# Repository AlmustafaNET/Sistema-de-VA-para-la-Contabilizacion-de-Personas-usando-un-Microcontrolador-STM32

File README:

# Este es mi README

<b> hola  </b>

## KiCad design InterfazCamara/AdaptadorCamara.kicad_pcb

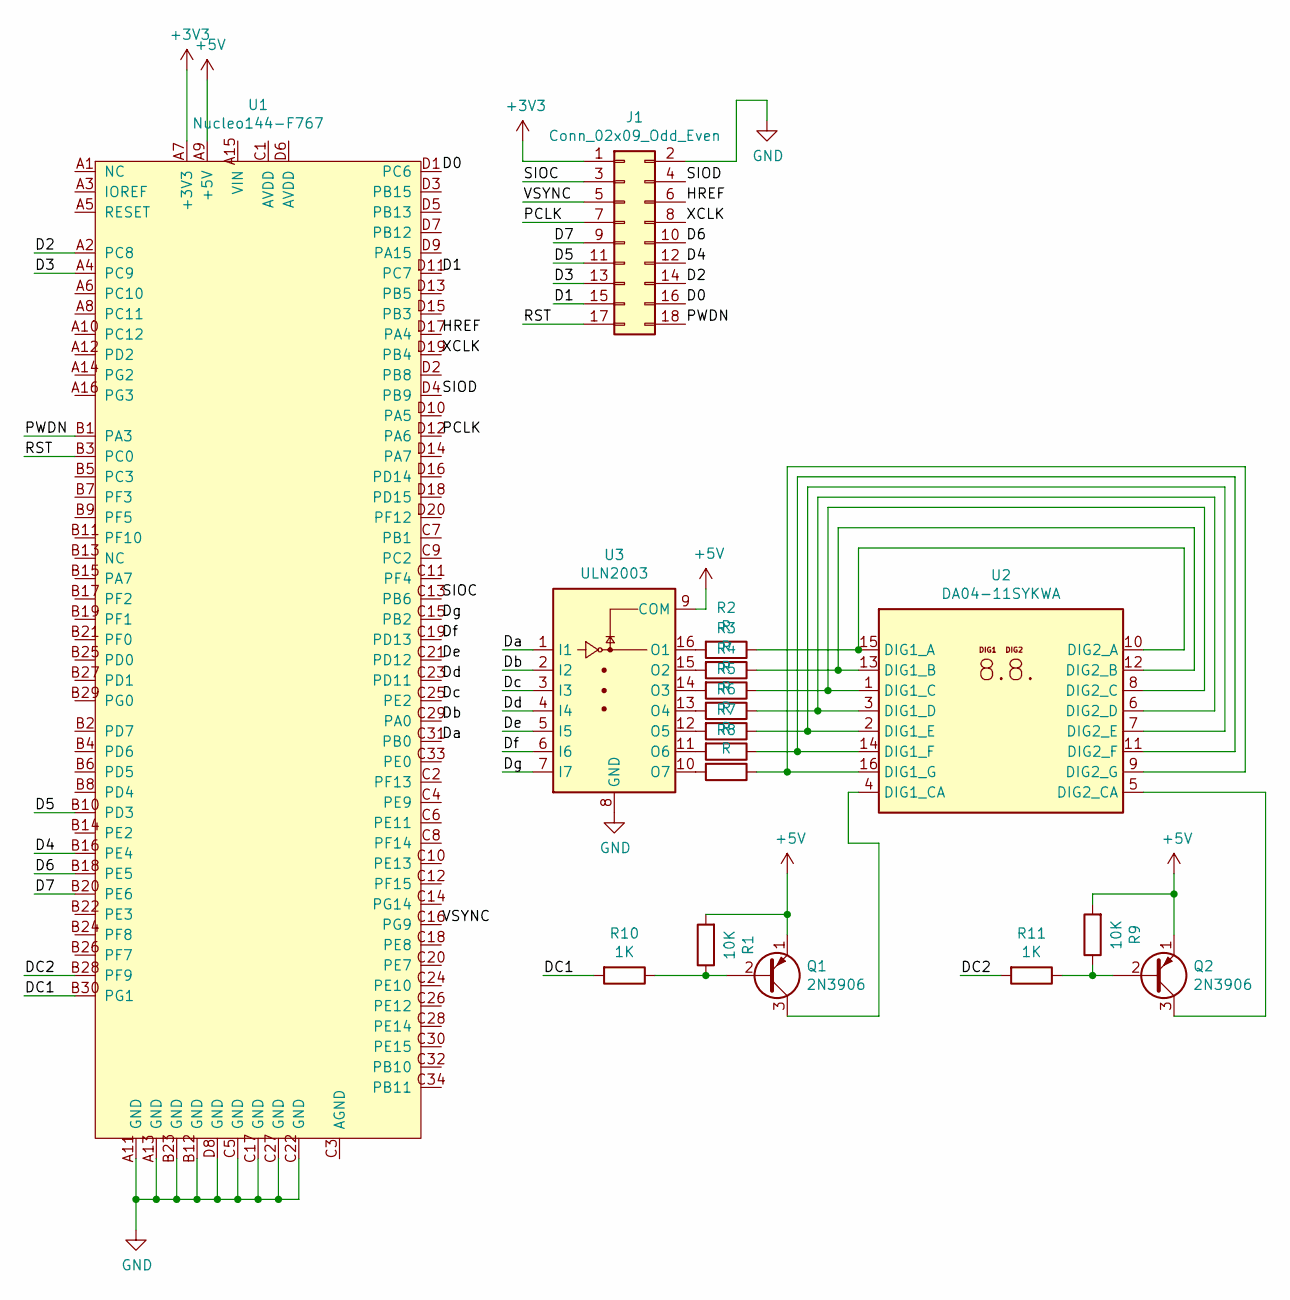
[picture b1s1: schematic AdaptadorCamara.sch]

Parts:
J1: Conn_02x09_Odd_Even; PinHeader_2x09_P2.54mm_Vertical
Q1, Q2: 2N3906; TO-92_Inline
R1, R9: 10K; R_1206_3216Metric_Pad1.42x1.75mm_HandSolder
R2, R3, R4, R5, R6, R7, R8: R; R_1206_3216Metric_Pad1.42x1.75mm_HandSolder
R10, R11: 1K; R_1206_3216Metric_Pad1.42x1.75mm_HandSolder
U1: Nucleo144-F767; STM-NUCLEO144-F767
U2: DA04-11SYKWA
U3: ULN2003; SOIC-16W_5.3x10.2mm_Pitch1.27mm

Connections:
+3V3: J1.1, U1.A7 (+3V3)
+5V: Q1.1 (E), Q2.1 (E), R1.2, R9.2, U1.A9 (+5V), U3.9 (COM)
/D0: J1.16, U1.D1 (PC6)
/D1: J1.15, U1.D11 (PC7)
/D2: J1.14, U1.A2 (PC8)
/D3: J1.13, U1.A4 (PC9)
/D4: J1.12, U1.B16 (PE4)
/D5: J1.11, U1.B10 (PD3)
/D6: J1.10, U1.B18 (PE5)
/D7: J1.9, U1.B20 (PE6)
/DC1: R10.2, U1.B30 (PG1)
/DC2: R11.2, U1.B28 (PF9)
/Da: U1.C31 (PB0), U3.1 (I1)
/Db: U1.C29 (PA0), U3.2 (I2)
/Dc: U1.C25 (PE2), U3.3 (I3)
/Dd: U1.C23 (PD11), U3.4 (I4)
/De: U1.C21 (PD12), U3.5 (I5)
/Df: U1.C19 (PD13), U3.6 (I6)
/Dg: U1.C15 (PB2), U3.7 (I7)
/HREF: J1.6, U1.D17 (PA4)
/PCLK: J1.7, U1.D12 (PA6)
/PWDN: J1.18, U1.B1 (PA3)
/RST: J1.17, U1.B3 (PC0)
/SIOC: J1.3, U1.C13 (PB6)
/SIOD: J1.4, U1.D4 (PB9)
/VSYNC: J1.5, U1.C16 (PG9)
/XCLK: J1.8, U1.D19 (PB4)
GND: J1.2, U1.A11 (GND), U1.A13 (GND), U1.B12 (GND), U1.B23 (GND), U1.C5 (GND), U1.C17 (GND), U1.C22 (GND), U1.C27 (GND), U1.D8 (GND), U3.8 (GND)
unnamed: Q1.2 (B), R1.1, R10.1
unnamed: Q1.3 (C), U2.4 (DIG1_CA)
unnamed: Q2.2 (B), R9.1, R11.1
unnamed: Q2.3 (C), U2.5 (DIG2_CA)
unnamed: R2.1, U2.10 (DIG2_A), U2.15 (DIG1_A)
unnamed: R2.2, U3.16 (O1)
unnamed: R3.1, U2.12 (DIG2_B), U2.13 (DIG1_B)
unnamed: R3.2, U3.15 (O2)
unnamed: R4.1, U2.1 (DIG1_C), U2.8 (DIG2_C)
unnamed: R4.2, U3.14 (O3)
unnamed: R5.1, U2.3 (DIG1_D), U2.6 (DIG2_D)
unnamed: R5.2, U3.13 (O4)
unnamed: R6.1, U2.2 (DIG1_E), U2.7 (DIG2_E)
unnamed: R6.2, U3.12 (O5)
unnamed: R7.1, U2.11 (DIG2_F), U2.14 (DIG1_F)
unnamed: R7.2, U3.11 (O6)
unnamed: R8.1, U2.9 (DIG2_G), U2.16 (DIG1_G)
unnamed: R8.2, U3.10 (O7)

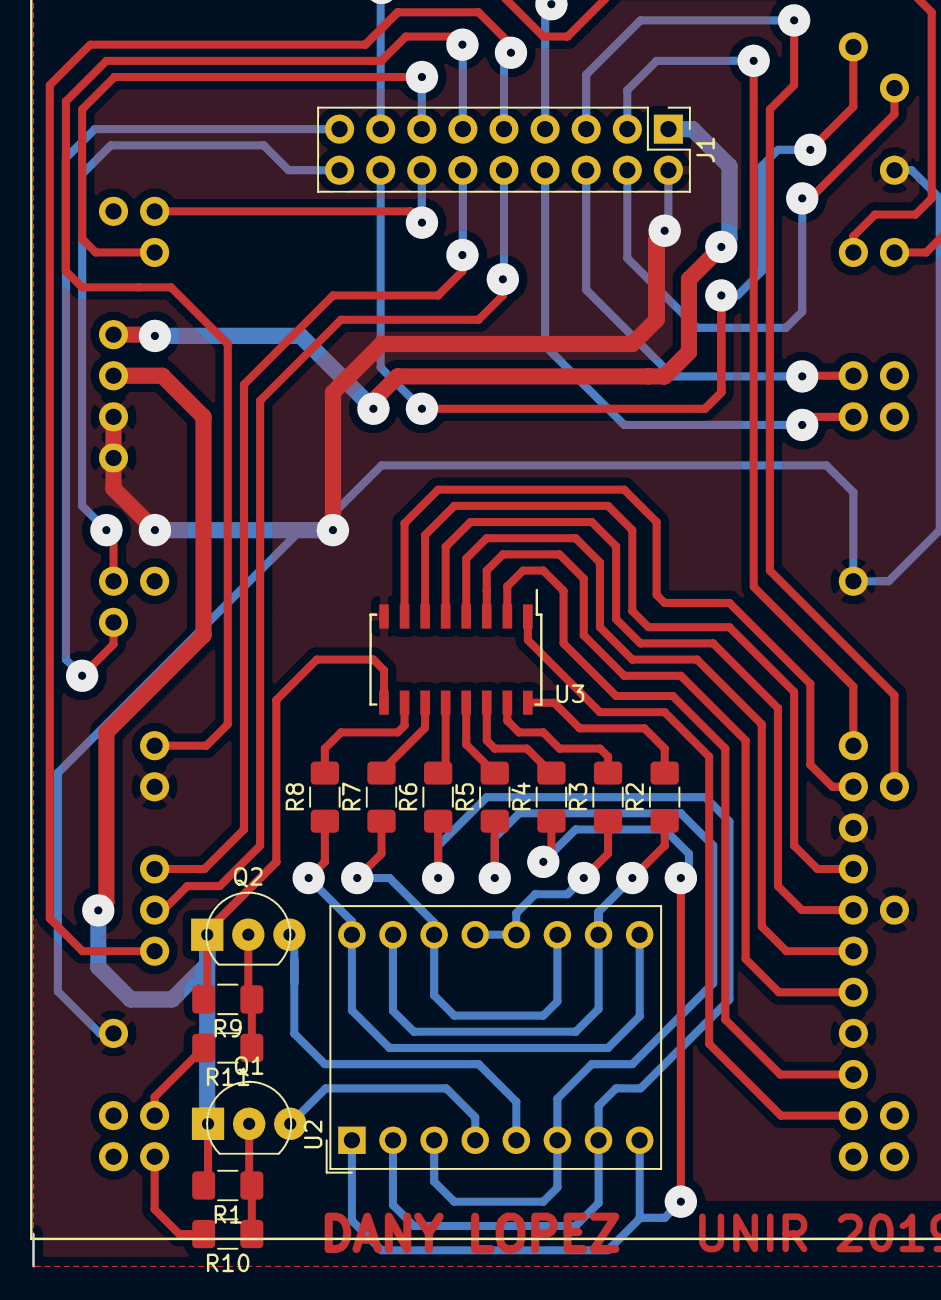
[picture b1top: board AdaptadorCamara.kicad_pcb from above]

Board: 2 copper layers, 17 parts (0 on the bottom side), 46 nets.

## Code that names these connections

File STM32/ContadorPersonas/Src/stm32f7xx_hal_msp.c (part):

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    __HAL_RCC_GPIOD_CLK_ENABLE();
    __HAL_RCC_GPIOG_CLK_ENABLE();
    /**DCMI GPIO Configuration    
    PE4     ------> DCMI_D4
    PE5     ------> DCMI_D6
    PE6     ------> DCMI_D7
    PA4     ------> DCMI_HSYNC
    PA6     ------> DCMI_PIXCLK
    PC6     ------> DCMI_D0
    PC7     ------> DCMI_D1
    PC8     ------> DCMI_D2
    PC9     ------> DCMI_D3
    PD3     ------> DCMI_D5
    PG9     ------> DCMI_VSYNC 
    */
    GPIO_InitStruct.Pin = GPIO_PIN_4|GPIO_PIN_5|GPIO_PIN_6;
    GPIO_InitStruct.Mode = GPIO_MODE_AF_PP;
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    __HAL_RCC_DCMI_CLK_DISABLE();
  
    /**DCMI GPIO Configuration    
    PE4     ------> DCMI_D4
    PE5     ------> DCMI_D6
    PE6     ------> DCMI_D7
    PA4     ------> DCMI_HSYNC
    PA6     ------> DCMI_PIXCLK
    PC6     ------> DCMI_D0
    PC7     ------> DCMI_D1
    PC8     ------> DCMI_D2
    PC9     ------> DCMI_D3
    PD3     ------> DCMI_D5
    PG9     ------> DCMI_VSYNC 
    */
    HAL_GPIO_DeInit(GPIOE, GPIO_PIN_4|GPIO_PIN_5|GPIO_PIN_6);

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  
    __HAL_RCC_GPIOB_CLK_ENABLE();
    /**I2C1 GPIO Configuration    
    PB6     ------> I2C1_SCL
    PB9     ------> I2C1_SDA 
    */
    GPIO_InitStruct.Pin = CAM_SIOC_Pin|CAM_SIOD_Pin;
    GPIO_InitStruct.Mode = GPIO_MODE_AF_OD;
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    __HAL_RCC_I2C1_CLK_DISABLE();
  
    /**I2C1 GPIO Configuration    
    PB6     ------> I2C1_SCL
    PB9     ------> I2C1_SDA 
    */
    HAL_GPIO_DeInit(GPIOB, CAM_SIOC_Pin|CAM_SIOD_Pin);

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  
    __HAL_RCC_GPIOB_CLK_ENABLE();
    /**TIM3 GPIO Configuration    
    PB4     ------> TIM3_CH1 
    */
    GPIO_InitStruct.Pin = GPIO_PIN_4;
    GPIO_InitStruct.Mode = GPIO_MODE_AF_PP;
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
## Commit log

2019-09-11 Readme
2019-09-11 Contador Personas en C
2019-09-11 Subiendo STM32 y ImagenPuertoSerial
2019-09-12 Videos
2019-09-12 TestComputador
2019-09-12 InterfazCamara
2019-09-12 InterfazCamara Readme
2019-09-18 Sin TCP
2020-03-06 `vallen` is verified to be less than `len`, therefore, it can never be the case that `vallen >= len + sizeof(rhostname)`.
    This PR fixes the check so the `rhostname` array does not overflow.
    Reported-by: Github Security Lab <securitylab@github.com>

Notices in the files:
STM32/ContadorPersonas/Src/stm32f7xx_hal_msp.c:
© Copyright (c) 2019 STMicroelectronics.
All rights reserved.
This software component is licensed by ST under BSD 3-Clause license,
the "License"; You may not use this file except in compliance with the
License. You may obtain a copy of the License at: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
(C) COPYRIGHT STMicroelectronics *****END OF FILE
